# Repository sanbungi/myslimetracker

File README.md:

# 3次元移動解析装置 改 — 乾電池駆動 SlimeVR トラッカー

VR ヘッドセットだけでは追跡できない足や腰の動きを取るための、自作 SlimeVR 互換フルボディトラッカーです。両足先・両膝・腰・胸の6点に装着し、VRChat 上でのフルトラッキングを実現しています。

- 単3乾電池駆動 — リチウムポリマー電池のリスクを避け、安全で入手しやすい乾電池で動作
- 最上級 IMU 搭載 — SlimeVR 対応 IMU の中で最高性能の LSM6DSV を採用
- 低コスト — mocopi（5万円〜）に対し、6トラッカーを合計約2万円で制作
- 高い拡張性 — SlimeVR はトラッカー数に制限がなく、必要に応じて増設可能

<p align="center"><i>現行基板の3Dレンダリング（KiCad）</i></p>

https://github.com/user-attachments/assets/3b7e9f30-eae3-4ba1-b326-60af60dc9e0d

<p align="center"><i>VRChat 内でのフルボディトラッキング動作</i></p>

## 乾電池へのこだわり

SlimeVR トラッカーの自作例はほとんどがリチウムポリマー電池を電源としていますが、本プロジェクトでは **単3乾電池** を採用しています。発火・膨張のリスクがなく、どこでも手に入り、近年は充電式乾電池（eneloop 等）も安価に出回っているため、ランニングコストも実用的です。

現行版は単3電池2本で動作し、昇圧 DC-DC コンバータで MCU・IMU に必要な電圧を供給しています。

## 基板設計

回路設計と基板レイアウトは KiCad で行い、製造は JLCPCB に発注しています。

| 部品 | 型番 | 役割 |
|------|------|------|
| MCU | Xiao ESP32-C3 | Wi-Fi 通信・SlimeVR ファームウェアの実行 |
| IMU | LSM6DSV | 6軸慣性計測（加速度 + ジャイロ） |
| 昇圧 DC-DC（現行） | 秋月電子 XCL103 キット | 単3x2 の電圧を 5V に昇圧 |
| 昇圧 DC-DC（次期） | TPS61291 | 単3x1 の電圧を 3.3V に昇圧 |

## 次期バージョン（WIP）

**単3乾電池1本** で駆動する次期基板を開発中です。昇圧回路・MCU・IMU を1枚の基板に統合し、さらなる小型化と軽量化を目指しています。就職活動のため一時中断中ですが、設計データは `new_prototype/` に格納しています。

---

## Gallery

### 6点トラッカーセット

*実際に運用中の6点セット（両足先・両膝・腰・胸）*

### JLCPCB から届いた基板

*JLCPCB に発注した基板の実物。*

### 次期基板 — 単3x1 実験（WIP）

*左: 単3乾電池1本用の次期統合基板 / 右: 部品実装後のイメージ*

### 現行基板（単3x2）

*KiCad 上での3Dレンダリング。昇圧ユニット・IMU・逆流防止回路を搭載。*

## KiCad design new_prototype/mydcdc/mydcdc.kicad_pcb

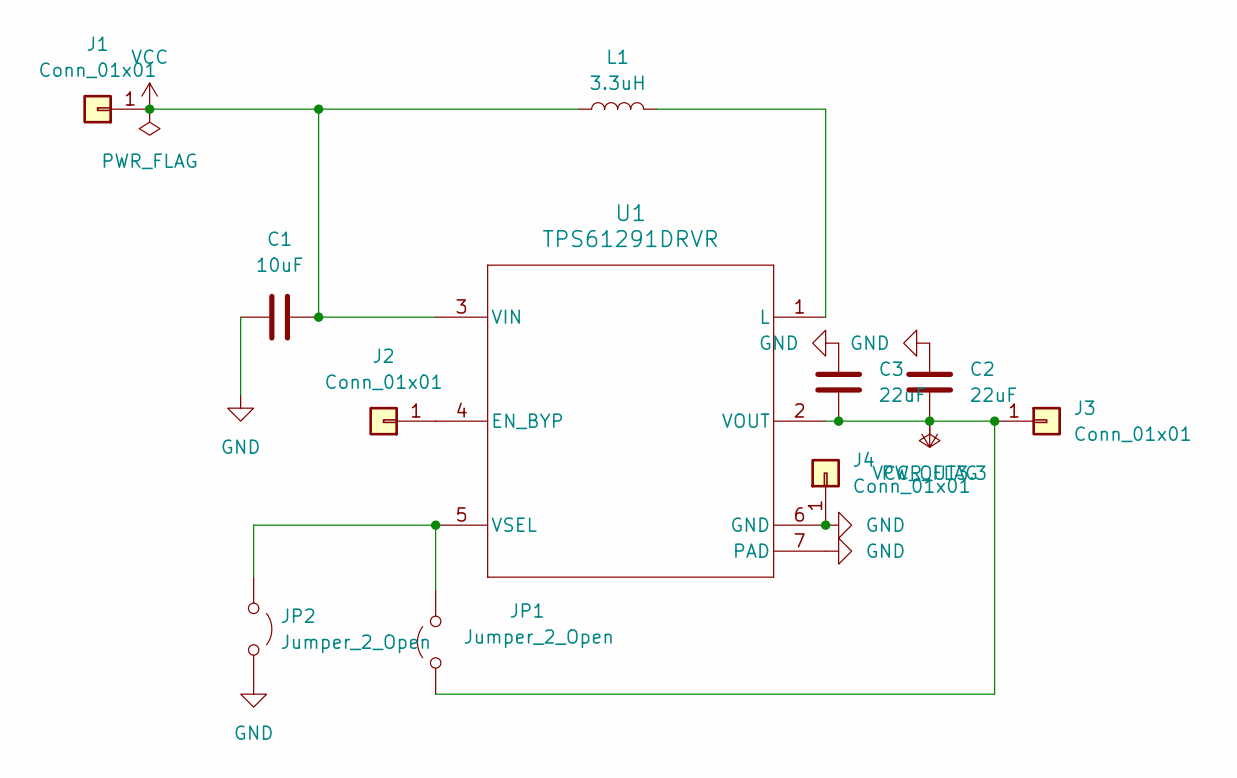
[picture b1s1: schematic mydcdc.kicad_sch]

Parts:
C1: 10uF; C_0805_2012Metric
C2, C3: 22uF; C_0805_2012Metric
J1, J2, J3, J4: Conn_01x01; PinHeader_1x01_P2.54mm_Vertical
JP1, JP2: Jumper_2_Open; SolderJumper-2_P1.3mm_Open_Pad1.0x1.5mm
L1: 3.3uH; L_Taiyo-Yuden_MD-3030
U1: TPS61291DRVR; DRV0006A

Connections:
GND: C1.1, C2.1, C3.1, J4.1, JP2.2 (B), U1.6 (GND), U1.7 (PAD); also elsewhere on the board
unnamed: J2.1, U1.4 (EN_BYP)
unnamed: JP1.1 (A), JP2.1 (A), U1.5 (VSEL)
unnamed: L1.2, U1.1 (L)
VCC: C1.2, J1.1, L1.1, U1.3 (VIN)
VCC_OUT3.3: C2.2, C3.2, J3.1, JP1.2 (B), U1.2 (VOUT)

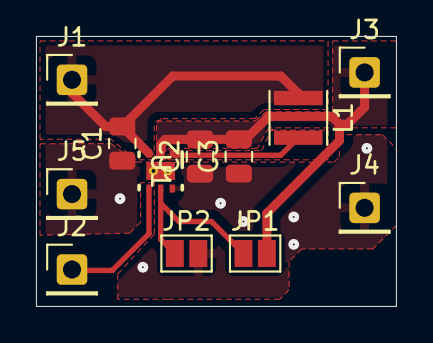
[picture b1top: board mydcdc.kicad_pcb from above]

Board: 2 copper layers, 20.0 x 15.0 mm, 12 parts (0 on the bottom side), 6 nets.

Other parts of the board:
J5: Conn_01x01; PinHeader_1x01_P2.54mm_Vertical

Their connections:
GND: J5.1; also elsewhere on the board

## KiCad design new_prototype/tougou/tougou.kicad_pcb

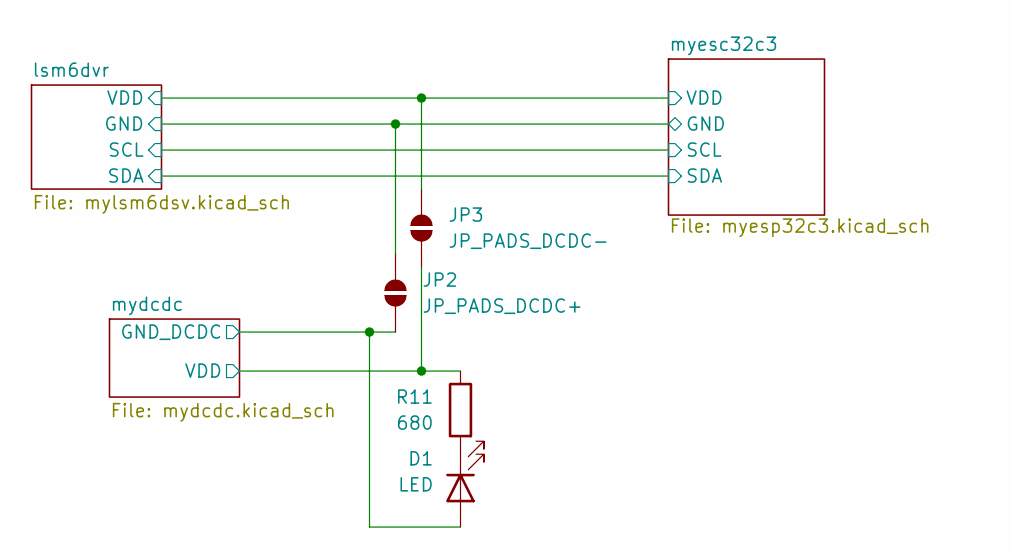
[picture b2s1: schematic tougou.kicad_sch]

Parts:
D1: LED; LED_0603_1608Metric
JP2: JP_PADS_DCDC+; SolderJumper-2_P1.3mm_Open_Pad1.0x1.5mm
JP3: JP_PADS_DCDC-; SolderJumper-2_P1.3mm_Open_Pad1.0x1.5mm
R11: 680; R_0603_1608Metric

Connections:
GND: JP2.2 (B); also elsewhere on the board
GND_DCDC: D1.2 (A), JP2.1 (A); also elsewhere on the board
unnamed: D1.1 (K), R11.2
VCC_OUT3.3: JP3.1 (A), R11.1; also elsewhere on the board
VDD: JP3.2 (B); also elsewhere on the board

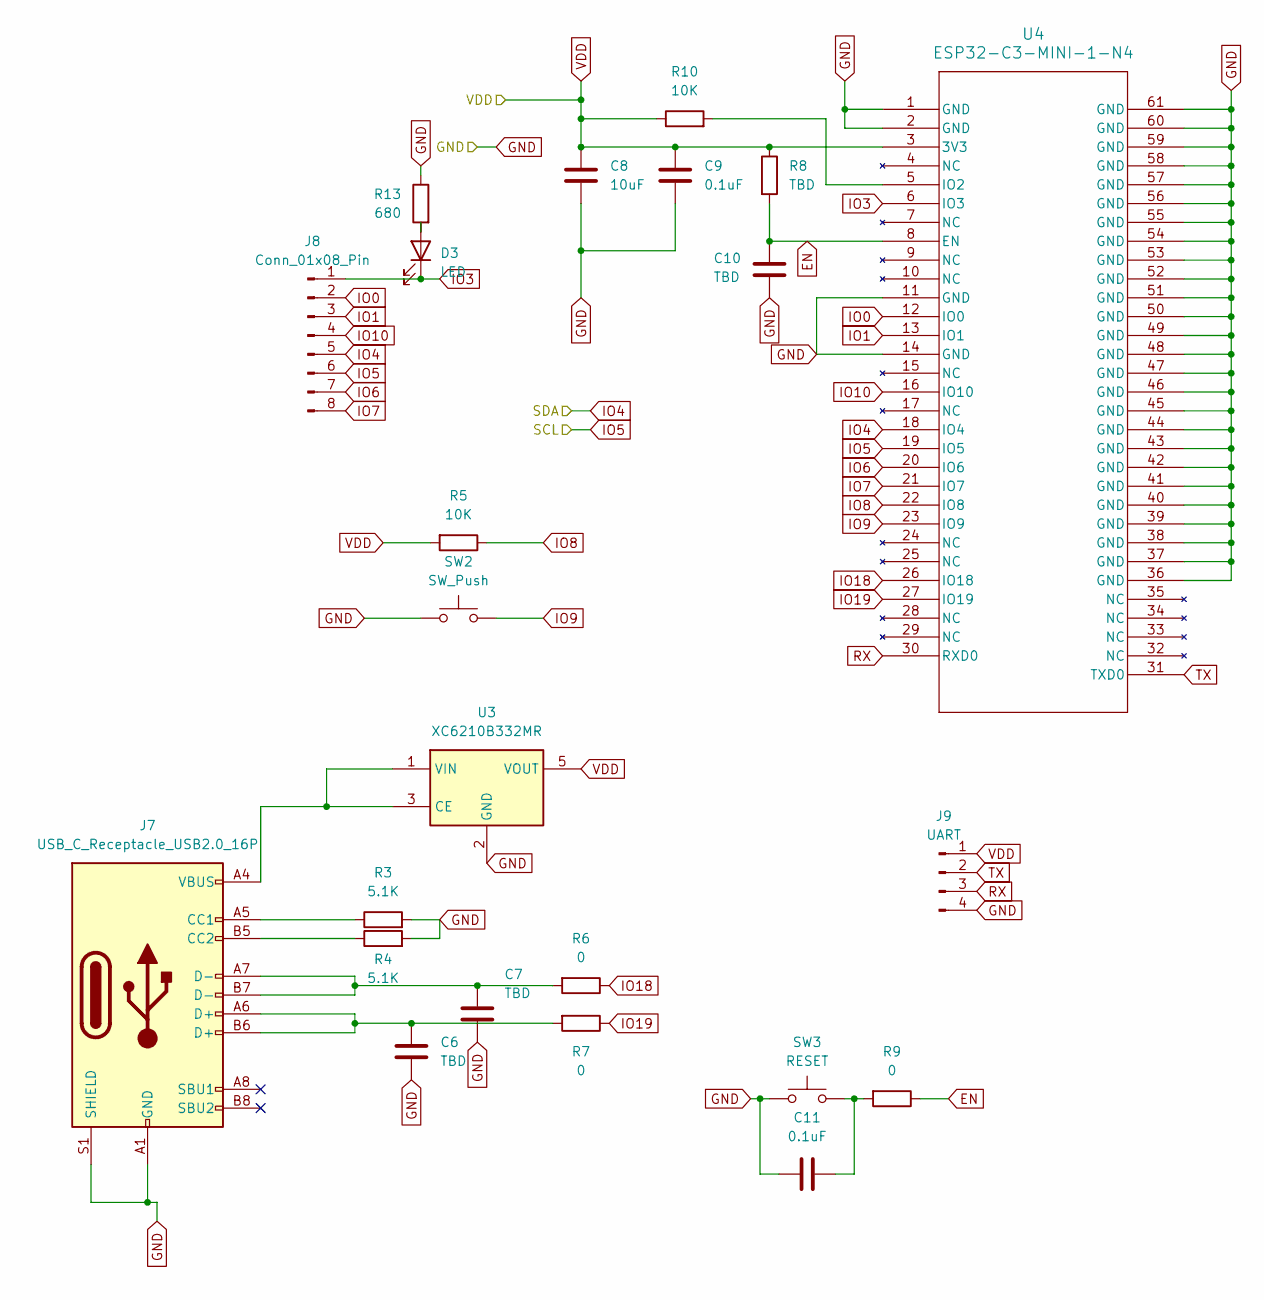
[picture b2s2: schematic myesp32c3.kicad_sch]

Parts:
C6, C7, C10: TBD; C_0603_1608Metric
C8: 10uF; C_0805_2012Metric
C9, C11: 0.1uF; C_0603_1608Metric
D3: LED; LED_0603_1608Metric
J7: USB_C_Receptacle_USB2.0_16P; USB_C_Receptacle_HCTL_HC-TYPE-C-16P-01A
J8: Conn_01x08_Pin; PinSocket_1x08_P2.54mm_Vertical
J9: UART; PinSocket_1x04_P2.54mm_Vertical
R3, R4: 5.1K; R_0603_1608Metric
R5, R10: 10K; R_0603_1608Metric
R6, R7, R9: 0; R_0603_1608Metric
R8: TBD; R_0603_1608Metric
R13: 680; R_0603_1608Metric
SW2: SW_Push; SW_Push_1P1T_NO_CK_KMR2
SW3: RESET; SW_Push_1P1T_NO_CK_KMR2
U3: XC6210B332MR; SOT-23-5
U4: ESP32-C3-MINI-1-N4; ESP32-C3-MINI-1_EXP

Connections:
EN: C10.1, R8.2, R9.1, U4.8 (EN)
GND: C6.2, C7.2, C8.2, C9.2, C10.2, C11.2, J7.A1 (GND), J7.A12 (GND), J7.B1 (GND), J7.B12 (GND), J7.S1 (SHIELD), J9.4, R3.2, R4.2, R13.1, SW2.1, SW3.1, U3.2 (GND), U4.1 (GND), U4.2 (GND), U4.11 (GND), U4.14 (GND), U4.36 (GND), U4.37 (GND), U4.38 (GND), U4.39 (GND), U4.40 (GND), U4.41 (GND), U4.42 (GND), U4.43 (GND), U4.44 (GND), U4.45 (GND), U4.46 (GND), U4.47 (GND), U4.48 (GND), U4.49 (GND), U4.50 (GND), U4.51 (GND), U4.52 (GND), U4.53 (GND), U4.54 (GND), U4.55 (GND), U4.56 (GND), U4.57 (GND), U4.58 (GND), U4.59 (GND), U4.60 (GND), U4.61 (GND); also elsewhere on the board
IO0: J8.2, U4.12 (IO0)
IO1: J8.3, U4.13 (IO1)
IO3: D3.1 (K), J8.1, U4.6 (IO3)
IO5: J8.6, U4.19 (IO5); also elsewhere on the board
IO6: J8.7, U4.20 (IO6)
IO7: J8.8, U4.21 (IO7)
IO8: R5.1, U4.22 (IO8)
IO9: SW2.2, U4.23 (IO9)
IO10: J8.4, U4.16 (IO10)
IO18: R6.1, U4.26 (IO18)
IO19: R7.1, U4.27 (IO19)
unnamed: C6.1, J7.A6 (D+), J7.B6 (D+), R7.2
unnamed: C7.1, J7.A7 (D-), J7.B7 (D-), R6.2
unnamed: C11.1, R9.2, SW3.2
unnamed: D3.2 (A), R13.2
unnamed: J7.A5 (CC1), R3.1
unnamed: J7.B5 (CC2), R4.1
unnamed: J7.A4 (VBUS), J7.A9 (VBUS), J7.B4 (VBUS), J7.B9 (VBUS), U3.1 (VIN), U3.3 (CE)
unnamed: R10.2, U4.5 (IO2)
RX: J9.3, U4.30 (RXD0)
SDA: J8.5, U4.18 (IO4); also elsewhere on the board
TX: J9.2, U4.31 (TXD0)
VDD: C8.1, C9.1, J9.1, R5.2, R8.1, R10.1, U3.5 (VOUT), U4.3 (3V3); also elsewhere on the board

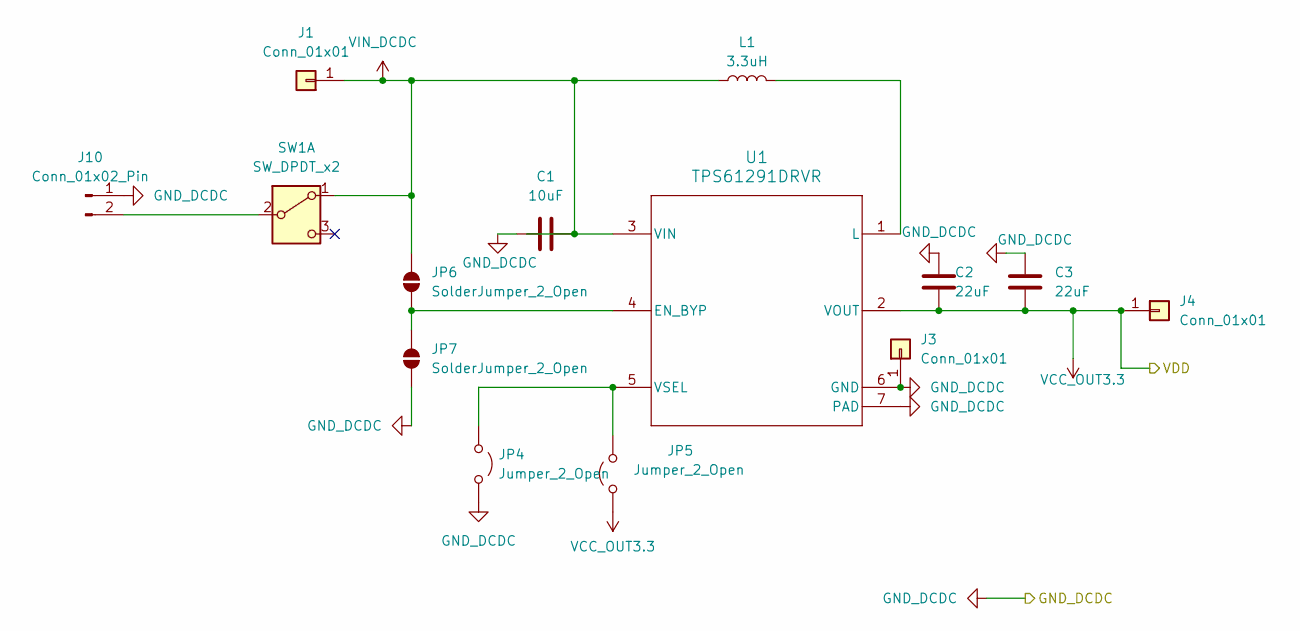
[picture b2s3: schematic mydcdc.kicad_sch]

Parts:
C1: 10uF; C_0805_2012Metric
C2, C3: 22uF; C_0805_2012Metric
J1, J3, J4: Conn_01x01; PinHeader_1x01_P2.54mm_Vertical
J10: Conn_01x02_Pin; PinHeader_1x02_P2.54mm_Vertical
JP4, JP5: Jumper_2_Open; SolderJumper-2_P1.3mm_Open_Pad1.0x1.5mm
JP6, JP7: SolderJumper_2_Open; SolderJumper-2_P1.3mm_Open_Pad1.0x1.5mm
L1: 3.3uH; L_Taiyo-Yuden_MD-3030
SW1: SW_DPDT_x2; SW_E-Switch_EG1271_SPDT
U1: TPS61291DRVR; DRV0006A

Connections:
GND_DCDC: C1.1, C2.1, C3.1, J3.1, J10.1, JP4.2 (B), JP7.1 (A), U1.6 (GND), U1.7 (PAD); also elsewhere on the board
unnamed: J10.2, SW1.2 (B)
unnamed: JP4.1 (A), JP5.1 (A), U1.5 (VSEL)
unnamed: JP6.1 (A), JP7.2 (B), U1.4 (EN_BYP)
unnamed: L1.2, U1.1 (L)
VCC_OUT3.3: C2.2, C3.2, J4.1, JP5.2 (B), U1.2 (VOUT); also elsewhere on the board
VIN_DCDC: C1.2, J1.1, JP6.2 (B), L1.1, SW1.1 (A), U1.3 (VIN)

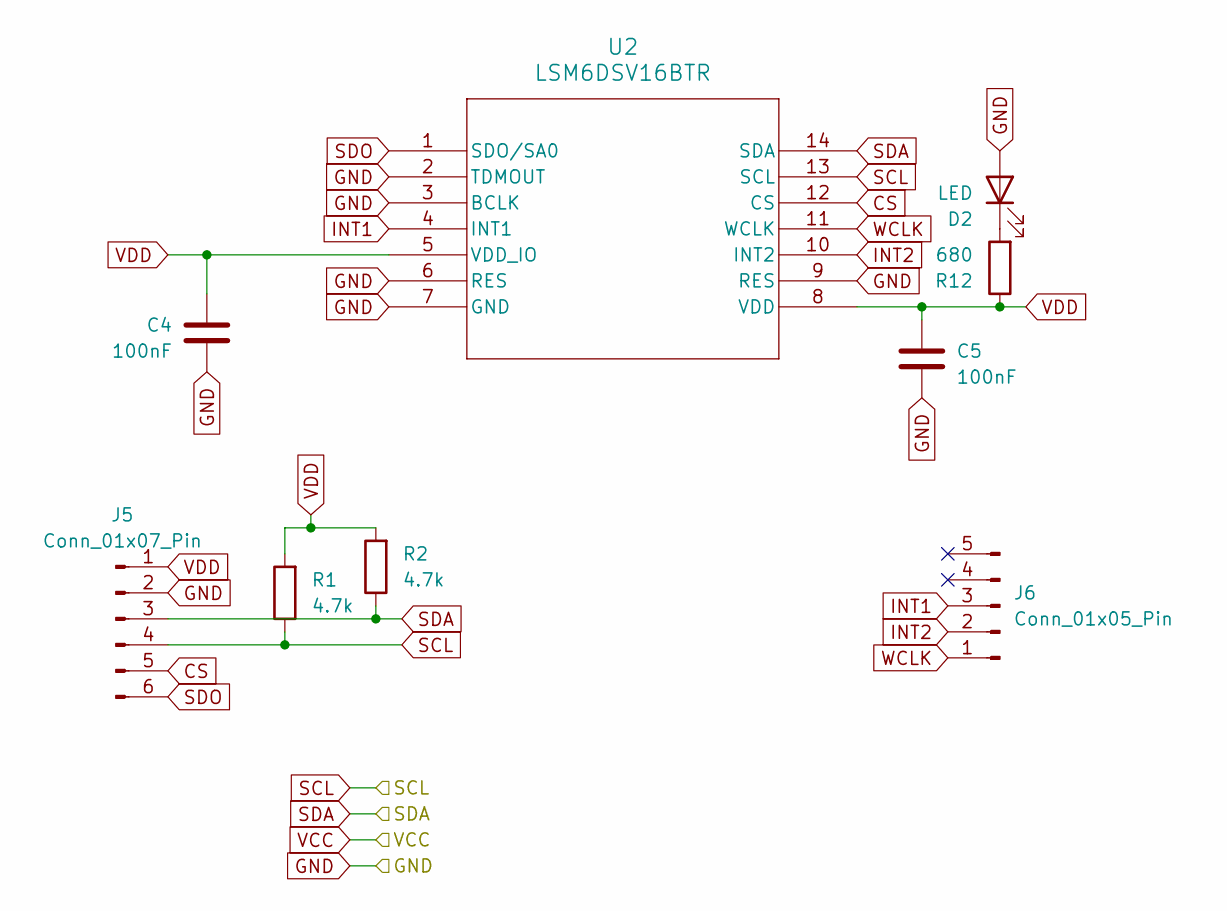
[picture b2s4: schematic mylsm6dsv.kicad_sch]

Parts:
C4, C5: 100nF; C_0805_2012Metric
D2: LED; LED_0603_1608Metric
J5: Conn_01x07_Pin; PinHeader_1x07_P2.54mm_Vertical
J6: Conn_01x05_Pin; PinHeader_1x05_P2.54mm_Vertical
R1, R2: 4.7k; R_0805_2012Metric
R12: 680; R_0603_1608Metric
U2: LSM6DSV16BTR; LGA-14_3x2.5mm_P0.5mm_LayoutBorder3x4y

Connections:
CS: J5.5, U2.12 (CS)
GND: C4.2, C5.2, D2.2 (A), J5.2, U2.2 (TDMOUT), U2.3 (BCLK), U2.6 (RES), U2.7 (GND), U2.9 (RES); also elsewhere on the board
INT1: J6.3, U2.4 (INT1)
INT2: J6.2, U2.10 (INT2)
IO5: J5.4, R1.1, U2.13 (SCL); also elsewhere on the board
unnamed: D2.1 (K), R12.2
SDA: J5.3, R2.1, U2.14 (SDA); also elsewhere on the board
SDO: J5.6, U2.1 (SDO/SA0)
VDD: C4.1, C5.1, J5.1, R1.2, R2.2, R12.1, U2.5 (VDD_IO), U2.8 (VDD); also elsewhere on the board
WCLK: J6.1, U2.11 (WCLK)

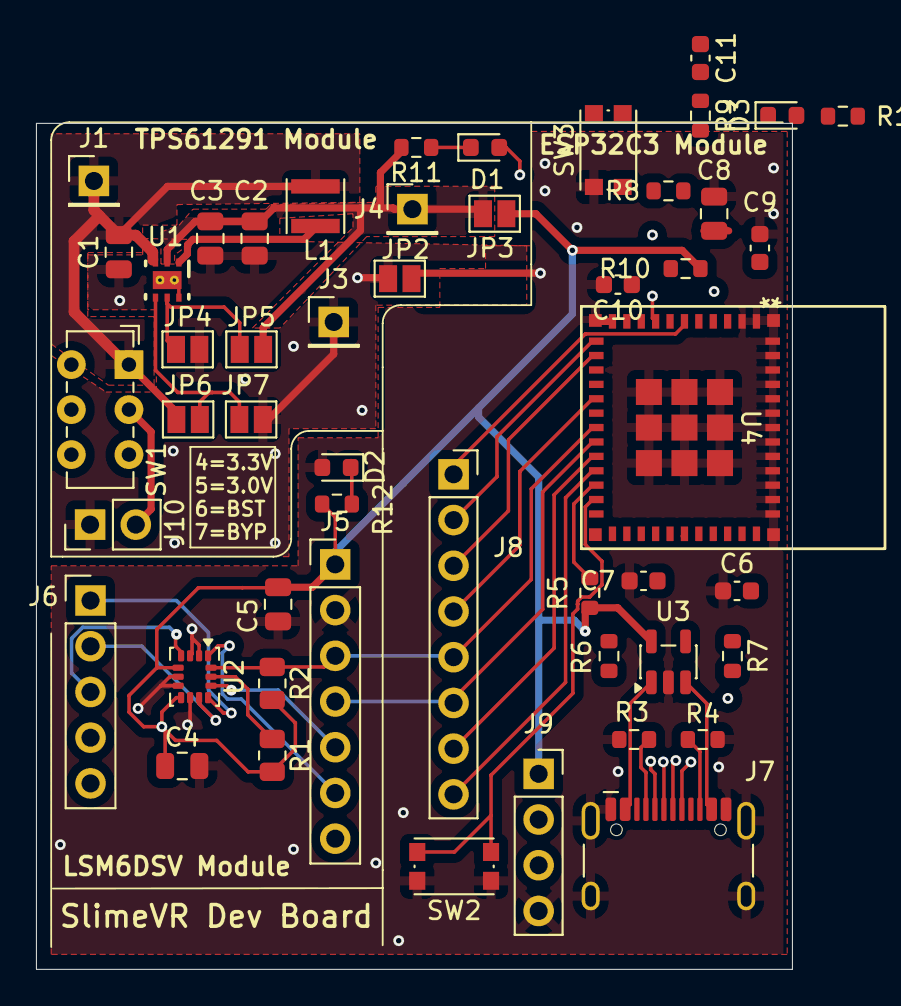
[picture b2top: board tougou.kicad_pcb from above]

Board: 2 copper layers, 42.0 x 47.0 mm, 50 parts (0 on the bottom side), 39 nets.

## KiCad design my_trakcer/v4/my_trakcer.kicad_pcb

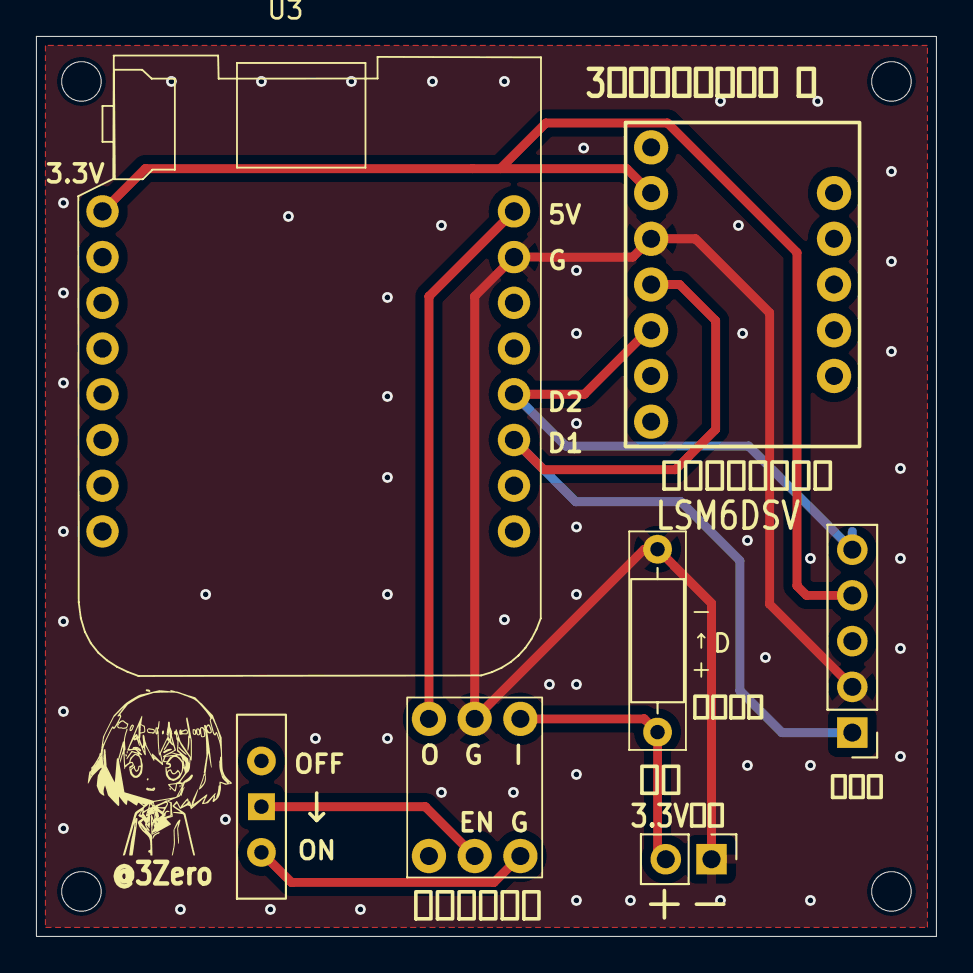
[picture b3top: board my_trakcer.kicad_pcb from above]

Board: 2 copper layers, 50.0 x 50.0 mm, 7 parts (0 on the bottom side), 8 nets.

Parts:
D: D; L_Axial_L6.6mm_D2.7mm_P10.16mm_Horizontal_Vishay_IM-2
D1: DCDC; AE-XCL103-5V0
J1: VIN; PinHeader_1x02_P2.54mm_Vertical
J2: 2nd; PinHeader_1x05_P2.54mm_Vertical
SW1: SW1; SW_Slide-03_Wuerth-WS-SLTV_10x2.5x6.4_P2.54mm
U1: LSM6DSV
U3: WeMos_mini; D1_mini_board

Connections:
3.3V: J2.4, U1.2 (3V3), U3.16 (3.3V)
GND: D.1 (K), D1.5 (GND), J1.1, J2.2, U1.3 (GND), U3.2 (GND)
unnamed: D1.2 (EN), SW1.1 (A)
unnamed: D1.4 (OUT), U3.1 (5V)
unnamed: D.2 (A), D1.6 (IN), J1.2
unnamed: D1.3 (GND), SW1.2 (B)
SCL: J2.1, U1.4 (SCL), U3.6 (D1)
SDA: J2.5, U1.5 (SDA), U3.5 (D2)

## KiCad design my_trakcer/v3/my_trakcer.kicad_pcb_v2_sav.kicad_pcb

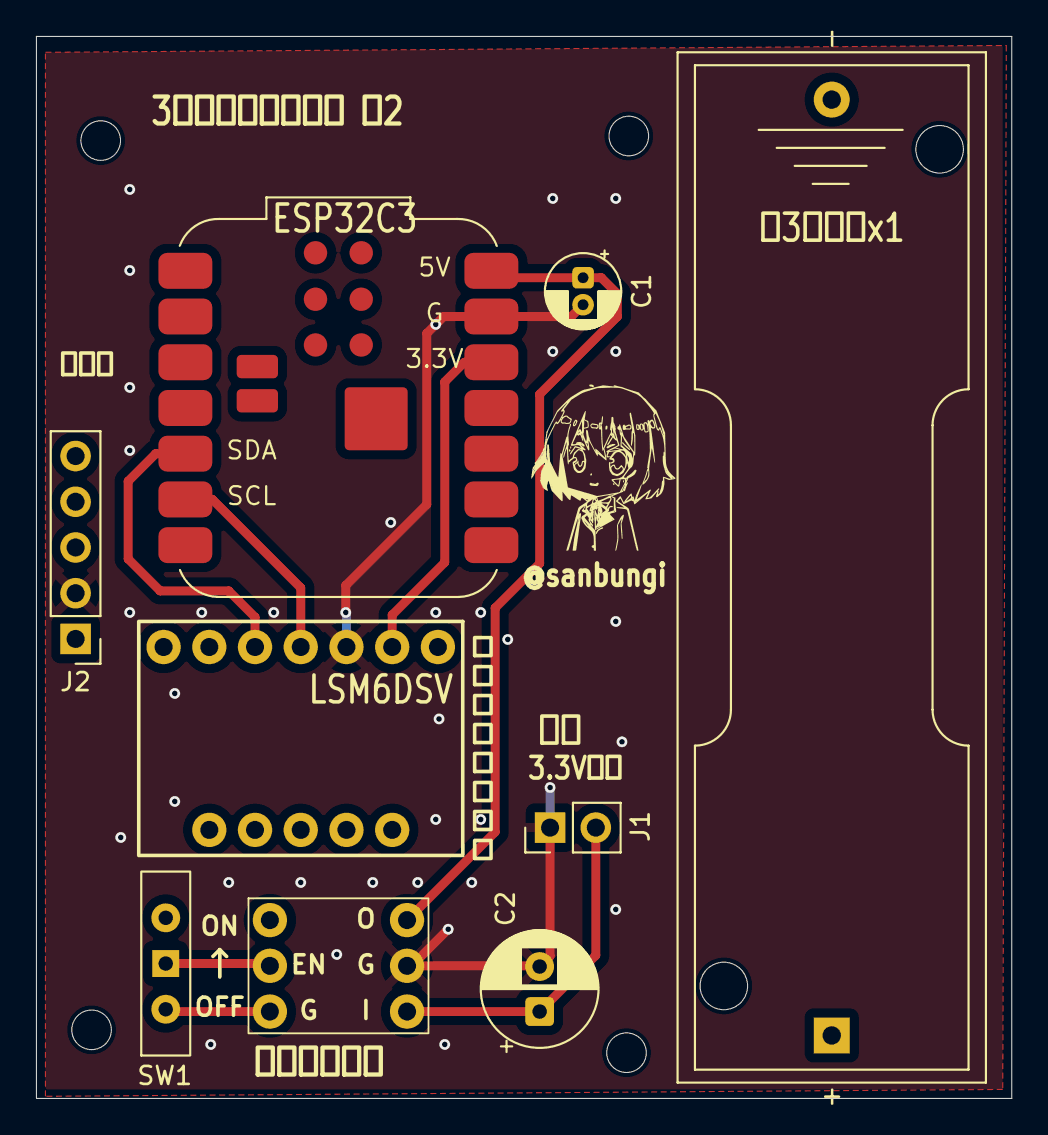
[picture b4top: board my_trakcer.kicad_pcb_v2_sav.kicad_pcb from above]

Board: 2 copper layers, 54.2 x 59.0 mm, 8 parts (0 on the bottom side), 8 nets.

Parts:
C1: C; CP_Radial_D4.0mm_P1.50mm
C2: C; CP_Radial_D6.3mm_P2.50mm
D2: AE-XCL103-5V02
J1: VIN; PinHeader_1x02_P2.54mm_Vertical
J2: 2nd; PinHeader_1x05_P2.54mm_Vertical
SW1: SW1; SW_Slide-03_Wuerth-WS-SLTV_10x2.5x6.4_P2.54mm
U2: XIAO-ESP32-C3-DIP; MCU_Seeed_ESP32C3
U3: LSM6DSV

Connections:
3.3V: J2.4, U2.12 (3V3), U3.2 (3V3)
GND: C1.2, C2.2, D2.5 (GND), J1.1, J2.2, U2.13 (GND), U3.3 (GND)
unnamed: D2.2 (EN), SW1.1 (A)
unnamed: C1.1, D2.4 (OUT), U2.14 (VBUS)
unnamed: C2.1, D2.6 (IN), J1.2
unnamed: D2.3 (GND), SW1.2 (B)
SCL: J2.1, U2.6 (GPIO7_D5_SCL), U3.4 (SCL)
SDA: J2.5, U2.5 (GPIO6_D4_SDA), U3.5 (SDA)

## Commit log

2026-03-12 kicadファイルを追加
2026-03-12 3dプリント用ファイルを追加
2026-03-12 gitignore
2026-03-12 slivemr要定義ファイル
2026-03-12 新規プロトタイププロジェクトをコピー
2026-03-12 紹介用画像
